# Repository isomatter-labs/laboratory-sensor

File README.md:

# isomatter-labs :: Laboratory Sensor

## Software
### Building
To build the firmware for the Laboratory Sensor, execute the following:
```sh
cd build
./build.sh
```

### Flashing
After building, there should be a `.uf2` file that can be dragged-and-dropped into a Raspberry Pi Pico.
This is the entirety of the firmware, and requires no additional steps.

## Electronics
### Editing
KiCAD files can be found in `hardware/printed_circuit_board/kicad_files`,
and can be edited or modified to provide any changes you wish to the hardware or layout.

(note that changing the overall footprint of the PCB will likely require changes to the enclosure files)

### Printing
Many PCB-printing services require only `gbr` files, which can be found at
`hardware/printed_circuit_board/gbr_files`.

These files can also be re-generated using the above mentioned KiCAD files and a working copy of KiCAD.

## Enclosure
Included in `hardware/enclosure` are a series of `.step` files, with one file per part.
These files can be sliced by most, if not all, slicers, and are a bit more resilient to paywalling by various CAD editors.

Also included is a file `render.png`, which should give a good idea of what the parts should look like,
and how they should fit together to form the enclosure.

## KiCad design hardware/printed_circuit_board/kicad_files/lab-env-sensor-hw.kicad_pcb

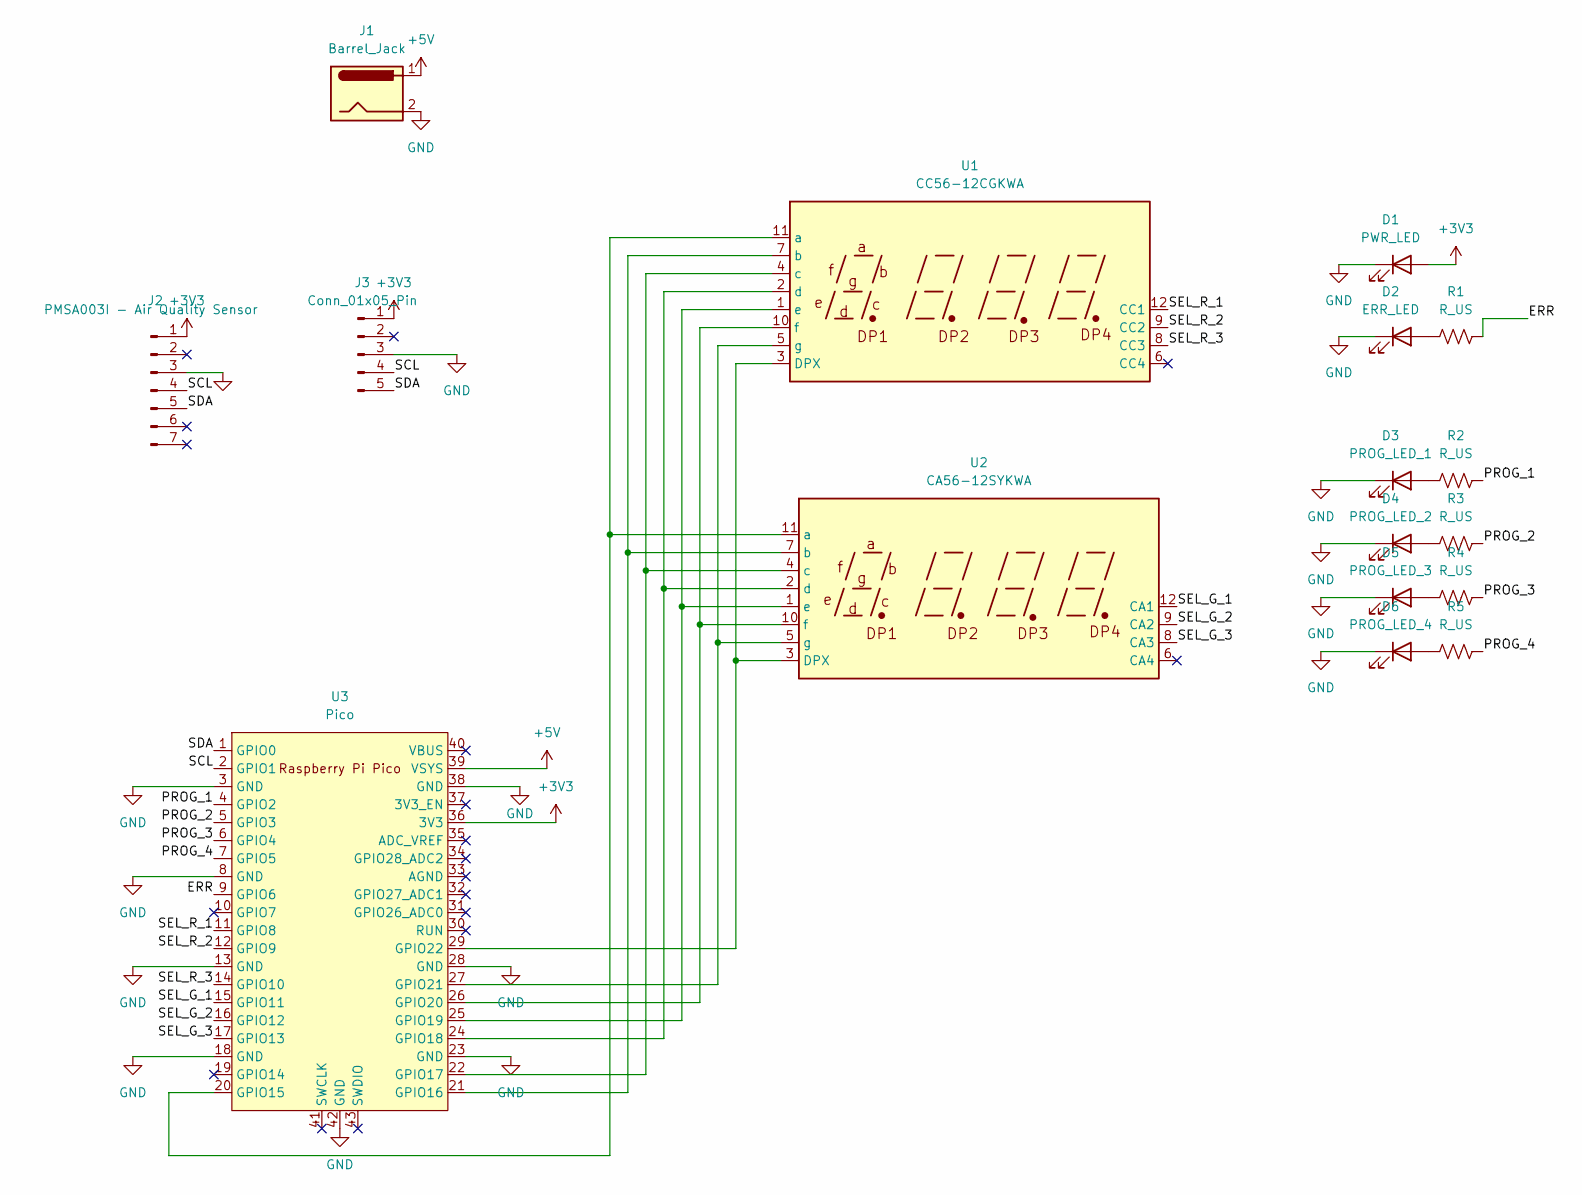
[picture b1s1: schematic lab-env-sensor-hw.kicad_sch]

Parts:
D1: PWR_LED; LED_D10.0mm
D2: ERR_LED; LED_D10.0mm
D3: PROG_LED_1; LED_D5.0mm
D4: PROG_LED_2; LED_D5.0mm
D5: PROG_LED_3; LED_D5.0mm
D6: PROG_LED_4; LED_D5.0mm
J1: Barrel_Jack; BarrelJack_Horizontal
J2: PMSA003I - Air Quality Sensor; PinSocket_1x07_P2.54mm_Vertical
J3: Conn_01x05_Pin; PinHeader_1x05_P2.54mm_Vertical
R1, R2, R3, R4, R5: R_US; R_Axial_DIN0207_L6.3mm_D2.5mm_P10.16mm_Horizontal
U1: CC56-12CGKWA; CA56-12CGKWA
U2: CA56-12SYKWA
U3: Pico; RPi_Pico_SMD_TH

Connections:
+3V3: D1.2 (A), J2.1 (VIN), J3.1, U3.36 (3V3)
+5V: J1.1, U3.39 (VSYS)
/ERR: R1.2, U3.9 (GPIO6)
/PROG_1: R2.2, U3.4 (GPIO2)
/PROG_2: R3.2, U3.5 (GPIO3)
/PROG_3: R4.2, U3.6 (GPIO4)
/PROG_4: R5.2, U3.7 (GPIO5)
/SCL: J2.4 (SCL), J3.4, U3.2 (GPIO1)
/SDA: J2.5 (SDA), J3.5, U3.1 (GPIO0)
/SEL_G_1: U2.12 (CA1), U3.15 (GPIO11)
/SEL_G_2: U2.9 (CA2), U3.16 (GPIO12)
/SEL_G_3: U2.8 (CA3), U3.17 (GPIO13)
/SEL_R_1: U1.12 (CC1), U3.11 (GPIO8)
/SEL_R_2: U1.9 (CC2), U3.12 (GPIO9)
/SEL_R_3: U1.8 (CC3), U3.14 (GPIO10)
GND: D1.1 (K), D2.1 (K), D3.1 (K), D4.1 (K), D5.1 (K), D6.1 (K), J1.2, J2.3 (GND), J3.3, U3.3 (GND), U3.8 (GND), U3.13 (GND), U3.18 (GND), U3.23 (GND), U3.28 (GND), U3.38 (GND), U3.42 (GND)
unnamed: D2.2 (A), R1.1
unnamed: D3.2 (A), R2.1
unnamed: D4.2 (A), R3.1
unnamed: D5.2 (A), R4.1
unnamed: D6.2 (A), R5.1
unnamed: U1.3 (DPX), U2.3 (DPX), U3.29 (GPIO22)
unnamed: U1.11 (a), U2.11 (a), U3.20 (GPIO15)
unnamed: U1.7 (b), U2.7 (b), U3.21 (GPIO16)
unnamed: U1.4 (c), U2.4 (c), U3.22 (GPIO17)
unnamed: U1.2 (d), U2.2 (d), U3.24 (GPIO18)
unnamed: U1.1 (e), U2.1 (e), U3.25 (GPIO19)
unnamed: U1.10 (f), U2.10 (f), U3.26 (GPIO20)
unnamed: U1.5 (g), U2.5 (g), U3.27 (GPIO21)

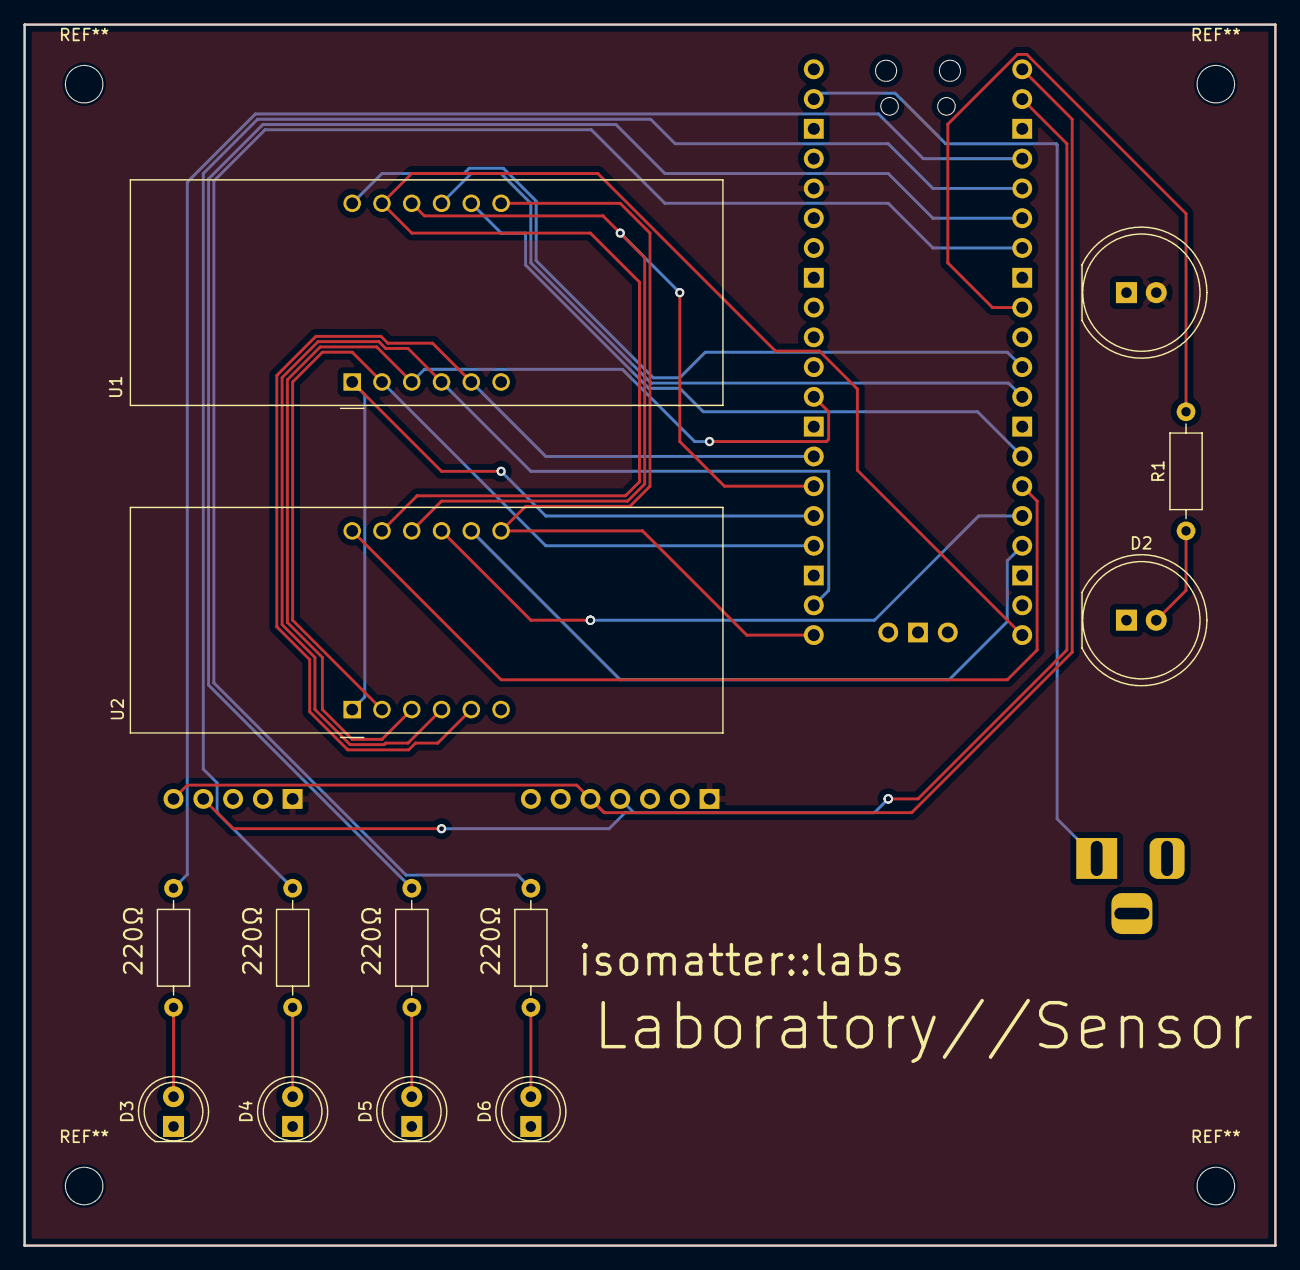
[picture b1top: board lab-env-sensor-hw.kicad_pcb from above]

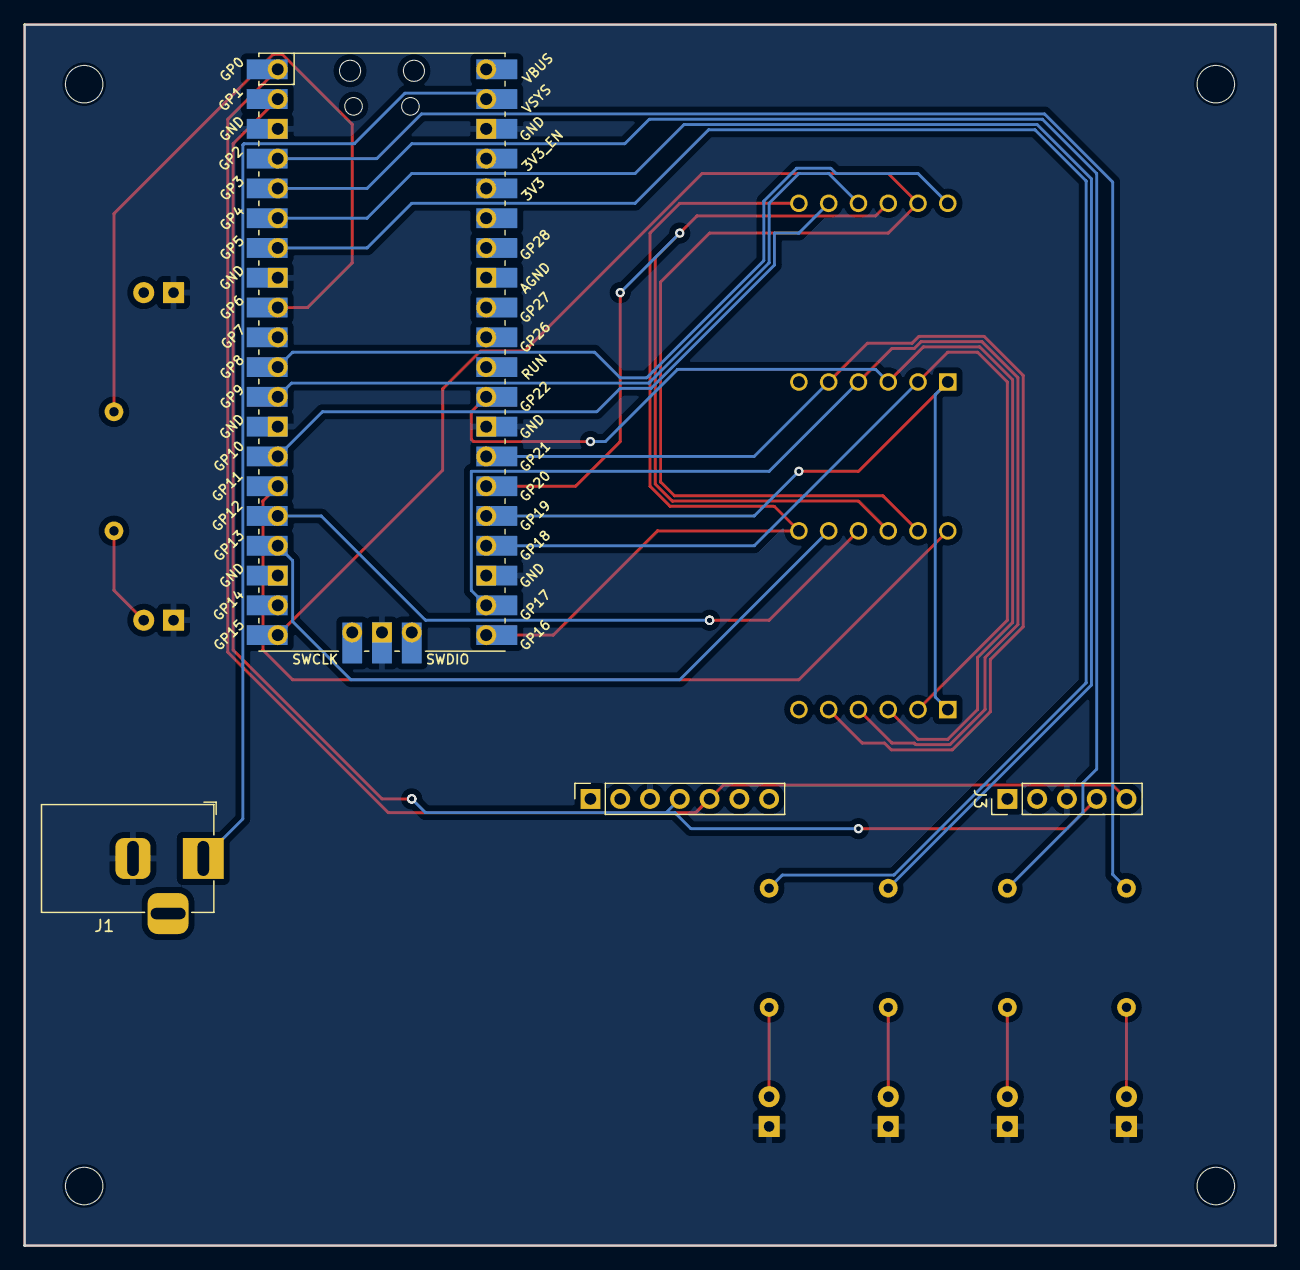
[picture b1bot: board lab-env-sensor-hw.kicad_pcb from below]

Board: 2 copper layers, 106.7 x 104.1 mm, 17 parts (4 on the bottom side), 29 nets.

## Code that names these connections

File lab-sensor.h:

#ifndef LAB_SENSOR_H
#define LAB_SENSOR_H

#include <inttypes.h>

#define DELAY_TIME 3

/* PINS */
#define LED 25
#define ERR 6
#define BUZZ 7
#define SDA 0
#define SCL 1
#define PROG_1 2
#define PROG_2 3
#define PROG_3 4
#define PROG_4 5
/* END PINS */

/* PORTS */
#define DATA 15

#define SEL 6
/* END PORTS */

enum display_t {
  GRN,
  RED,
  END,
};

void err();
void write_to_data(uint8_t byte);
void write_to_sel(uint8_t byte);
void parse_digits(display_t display, float raw_val);
void display_digits();

#endif

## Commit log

2023-07-04 Add base files
2023-07-04 Add build script
2023-07-27 Add hardware
2023-07-27 Add 3mf file
2023-07-27 Add render, rather than 3mf
2023-07-27 Add PCB render
2023-07-28 Update enclosure
